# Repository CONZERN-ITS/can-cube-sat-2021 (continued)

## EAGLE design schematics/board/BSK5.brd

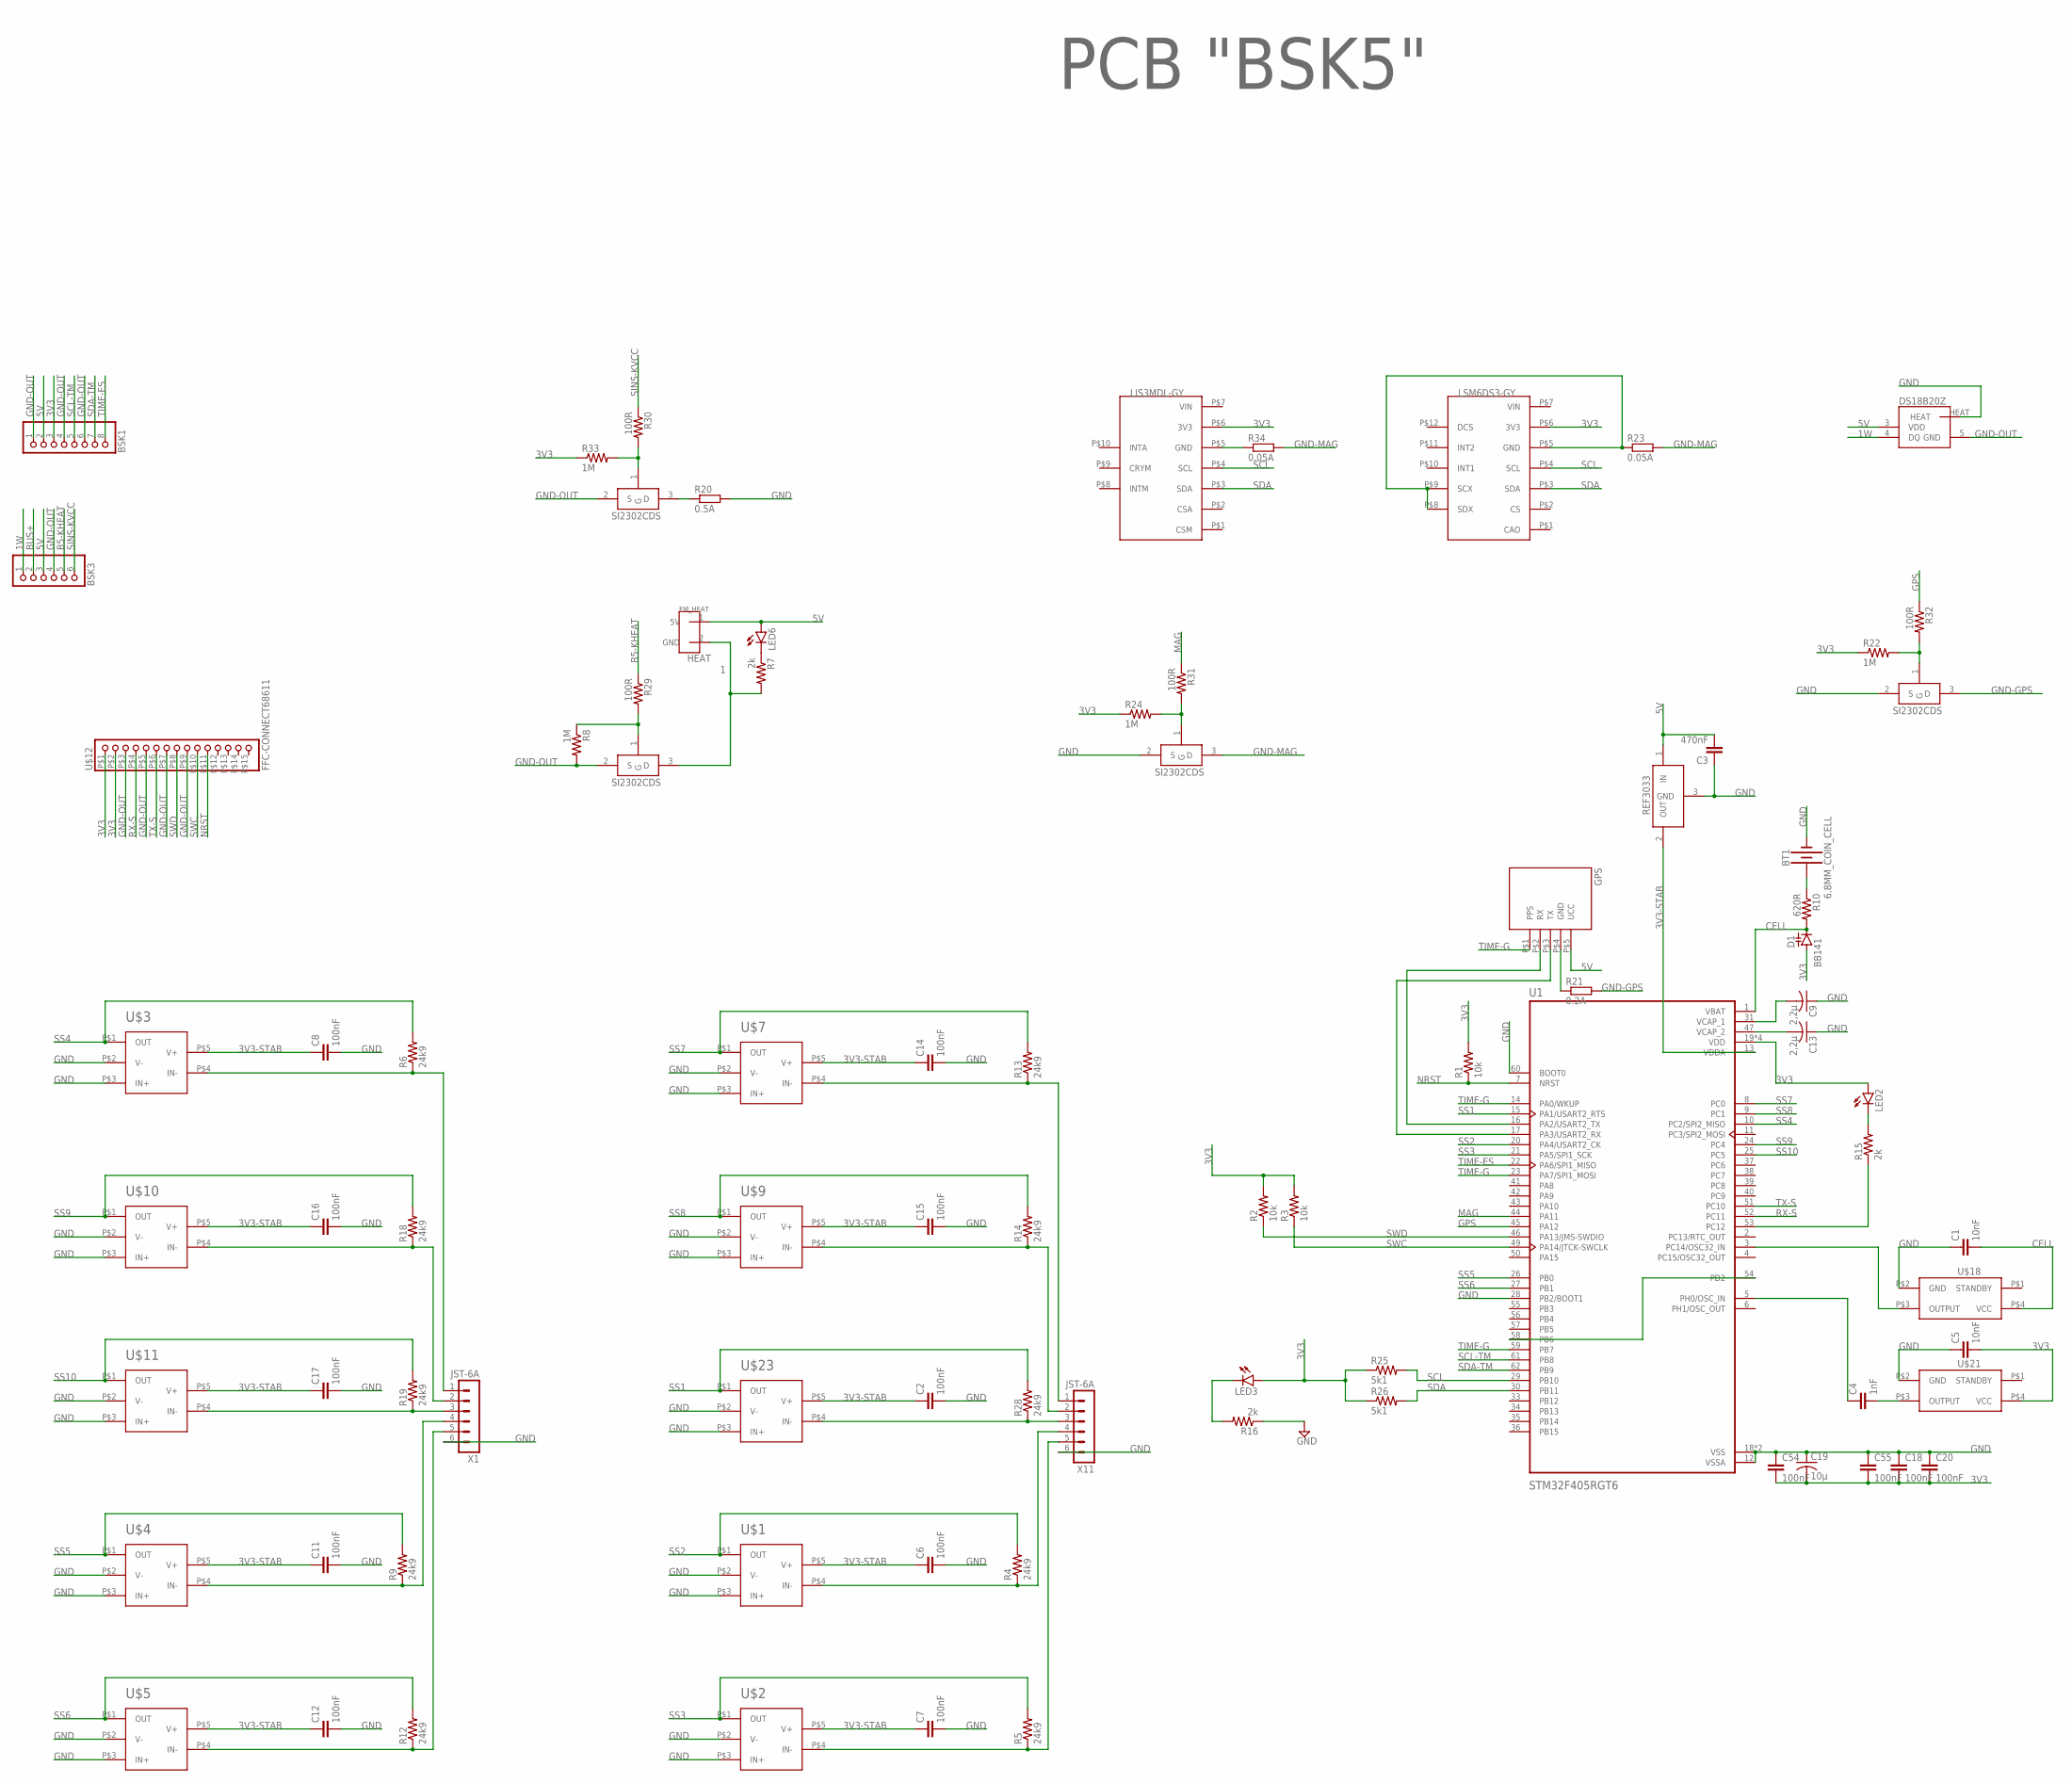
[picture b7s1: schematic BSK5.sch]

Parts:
BSK1: PINHD-1X8; 1X08
BSK3: PINHD-1X6; 1X06
BT1: 6.8MM_COIN_CELL; BATTCON-6.8MM
C1, C5: 10nF; C0603
C2, C6, C7, C8, C11, C12, C14, C15, C16, C17, C18, C20, C54, C55: 100nF; C0603
C3: 470nF; C0603
C4: 1nF; C0603
C9, C13: 2,2µ; C0603
C19: 10µ; C1206
D1: BB141; SOD523
DS18B20Z1: DS18B20Z; SOIC8+HEAT_S
GPS: GPSNEO6M; GPS-NEO6M
LED2, LED3, LED6: LEDCHIPLED_0603; CHIPLED_0603
LIS3MDL-GY: LIS3MDL-GY
LSM6DS3-GY: LSM6DS3-GY
R1, R2, R3: 10k; R0603
R4, R5, R6, R9, R12, R13, R14, R18, R19, R28: 24k9; R0603
R7, R15, R16: 2k; R0603
R8, R22, R24, R33: 1M; R0603
R10: 620R; R0603
R20: 0.5A; R1210
R21: 0.2A; R1210
R23, R34: 0.05A; R1210
R25, R26: 5k1; R0603
R29, R30, R31, R32: 100R; R0603
U1: STM32F405RGT6; QFP50P1200X1200X160-64N
U$1, U$2, U$3, U$4, U$5, U$7, U$9, U$10, U$11, U$23: LMC7101
U$6: REF3033; SOT23-3
U$8, U$19, U$20, U$22: SI2302CDS; SOT23-3
U$12: FFC-CONNECT68611; 68611
U$14: EM_HEAT
U$18: Q32.768
U$21: Q24
U$26: PCB "BSK5"; ITS-LOGO
X1, X11: JST-6A; B6B-EH-A

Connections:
1: R7.2, U$8.3 (D), U$14.2 (GND)
1W: BSK3.1, DS18B20Z1.4 (DQ)
3V3: BSK1.3, C5.2, C18.2, C19.2, C20.2, C54.2, C55.2, D1.A, LED2.A, LED3.A, LIS3MDL-GY.P$6 (3V3), LSM6DS3-GY.P$6 (3V3), R1.2, R2.2, R3.2, R22.1, R24.1, R25.1, R26.1, R33.1, U1.19 (VDD), U1.32 (VDD), U1.48 (VDD), U1.64 (VDD), U$12.P$1 (1), U$12.P$2 (2), U$21.P$4 (VCC)
3V3-STAB: C2.1, C6.1, C7.1, C8.1, C11.1, C12.1, C14.1, C15.1, C16.1, C17.1, U1.13 (VDDA), U$1.P$5 (V+), U$2.P$5 (V+), U$3.P$5 (V+), U$4.P$5 (V+), U$5.P$5 (V+), U$6.2 (OUT), U$7.P$5 (V+), U$9.P$5 (V+), U$10.P$5 (V+), U$11.P$5 (V+), U$23.P$5 (V+)
5V: BSK1.2, BSK3.3, C3.2, DS18B20Z1.3 (VDD), GPS.P$5 (UCC), LED6.A, U$6.1 (IN), U$14.1 (5V)
B5-KHEAT: BSK3.5, R29.1
BUS+: BSK3.2
CELL: C1.2, D1.C, R10.2, U1.1 (VBAT), U$18.P$4 (VCC)
GND: BT1.-, C1.1, C2.2, C3.1, C5.1, C6.2, C7.2, C8.2, C9.1, C11.2, C12.2, C13.1, C14.2, C15.2, C16.2, C17.2, C18.1, C19.1, C20.1, C54.1, C55.1, DS18B20Z1.HEAT, R16.1, R20.2, U1.12 (VSSA), U1.18 (VSS), U1.28 (PB2/BOOT1), U1.60 (BOOT0), U1.63 (VSS), U$1.P$2 (V-), U$1.P$3 (IN+), U$2.P$2 (V-), U$2.P$3 (IN+), U$3.P$2 (V-), U$3.P$3 (IN+), U$4.P$2 (V-), U$4.P$3 (IN+), U$5.P$2 (V-), U$5.P$3 (IN+), U$6.3 (GND), U$7.P$2 (V-), U$7.P$3 (IN+), U$9.P$2 (V-), U$9.P$3 (IN+), U$10.P$2 (V-), U$10.P$3 (IN+), U$11.P$2 (V-), U$11.P$3 (IN+), U$18.P$2 (GND), U$19.2 (S), U$20.2 (S), U$21.P$2 (GND), U$23.P$2 (V-), U$23.P$3 (IN+), X1.6, X11.6
GND-GPS: R21.2, U$20.3 (D)
GND-MAG: R23.2, R34.2, U$19.3 (D)
GND-OUT: BSK1.1, BSK1.4, BSK1.6, BSK3.4, DS18B20Z1.5 (GND), R8.2, U$8.2 (S), U$12.P$3 (3), U$12.P$5 (5), U$12.P$7 (7), U$12.P$9 (9), U$22.2 (S)
GPS: R32.1, U1.45 (PA12)
MAG: R31.1, U1.44 (PA11)
unnamed: U1.3 (PC14/OSC32_IN), U$18.P$3 (OUTPUT)
unnamed: R20.1, U$22.3 (D)
unnamed: R13.1, U$7.P$4 (IN-), X11.1
unnamed: R6.1, U$3.P$4 (IN-), X1.1
unnamed: R9.1, U$4.P$4 (IN-), X1.4
unnamed: R8.1, R29.2, U$8.1 (G)
unnamed: R30.2, R33.2, U$22.1 (G)
unnamed: R24.2, R31.2, U$19.1 (G)
unnamed: LSM6DS3-GY.P$5 (GND), LSM6DS3-GY.P$8 (SDX), LSM6DS3-GY.P$9 (SCX), R23.1
unnamed: R22.2, R32.2, U$20.1 (G)
unnamed: LIS3MDL-GY.P$5 (GND), R34.1
unnamed: BT1.+, R10.1
unnamed: GPS.P$4 (GND), R21.1
unnamed: U1.54 (PD2), U1.58 (PB6)
unnamed: C13.2, U1.47 (VCAP_2)
unnamed: R4.1, U$1.P$4 (IN-), X11.4
unnamed: R5.1, U$2.P$4 (IN-), X11.5
unnamed: LED6.C, R7.1
unnamed: R12.1, U$5.P$4 (IN-), X1.5
unnamed: C9.2, U1.31 (VCAP_1)
unnamed: LED2.C, R15.2
unnamed: R15.1, U1.53 (PC12)
unnamed: LED3.C, R16.2
unnamed: GPS.P$2 (RX), U1.16 (PA2/USART2_TX)
unnamed: GPS.P$3 (TX), U1.17 (PA3/USART2_RX)
unnamed: C4.2, U$21.P$3 (OUTPUT)
unnamed: C4.1, U1.5 (PH0/OSC_IN)
unnamed: R28.1, U$23.P$4 (IN-), X11.3
unnamed: R14.1, U$9.P$4 (IN-), X11.2
unnamed: R18.1, U$10.P$4 (IN-), X1.2
unnamed: R19.1, U$11.P$4 (IN-), X1.3
NRST: R1.1, U1.7 (NRST), U$12.P$11 (11)
RX-S: U1.52 (PC11), U$12.P$4 (4)
SCL: LIS3MDL-GY.P$4 (SCL), LSM6DS3-GY.P$4 (SCL), R25.2, U1.29 (PB10)
SCL-TM: BSK1.5, U1.61 (PB8)
SDA: LIS3MDL-GY.P$3 (SDA), LSM6DS3-GY.P$3 (SDA), R26.2, U1.30 (PB11)
SDA-TM: BSK1.7, U1.62 (PB9)
SINS-KVCC: BSK3.6, R30.1
SS1: R28.2, U1.15 (PA1/USART2_RTS), U$23.P$1 (OUT)
SS2: R4.2, U1.20 (PA4/USART2_CK), U$1.P$1 (OUT)
SS3: R5.2, U1.21 (PA5/SPI1_SCK), U$2.P$1 (OUT)
SS4: R6.2, U1.10 (PC2/SPI2_MISO), U$3.P$1 (OUT)
SS5: R9.2, U1.26 (PB0), U$4.P$1 (OUT)
SS6: R12.2, U1.27 (PB1), U$5.P$1 (OUT)
SS7: R13.2, U1.8 (PC0), U$7.P$1 (OUT)
SS8: R14.2, U1.9 (PC1), U$9.P$1 (OUT)
SS9: R18.2, U1.24 (PC4), U$10.P$1 (OUT)
SS10: R19.2, U1.25 (PC5), U$11.P$1 (OUT)
SWC: R3.1, U1.49 (PA14/JTCK-SWCLK), U$12.P$10 (10)
SWD: R2.1, U1.46 (PA13/JMS-SWDIO), U$12.P$8 (8)
TIME-ES: BSK1.8, U1.22 (PA6/SPI1_MISO)
TIME-G: GPS.P$1 (PPS), U1.14 (PA0/WKUP), U1.23 (PA7/SPI1_MOSI), U1.59 (PB7)
TX-S: U1.51 (PC10), U$12.P$6 (6)

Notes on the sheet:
HEAT

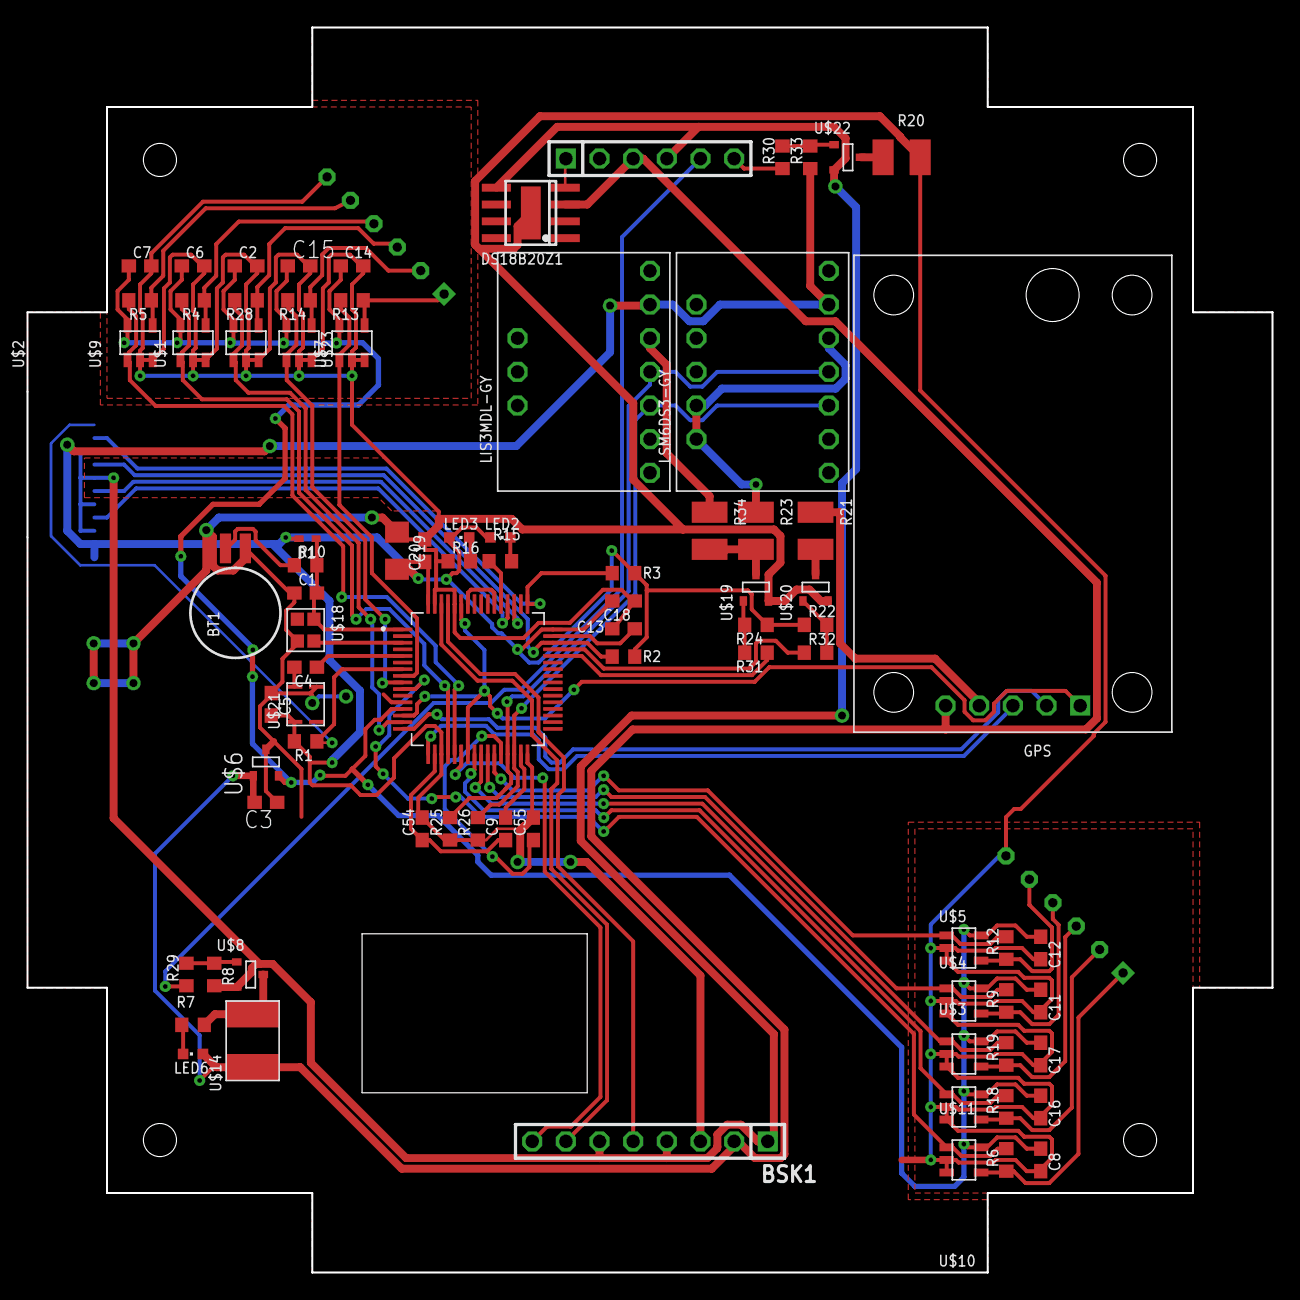
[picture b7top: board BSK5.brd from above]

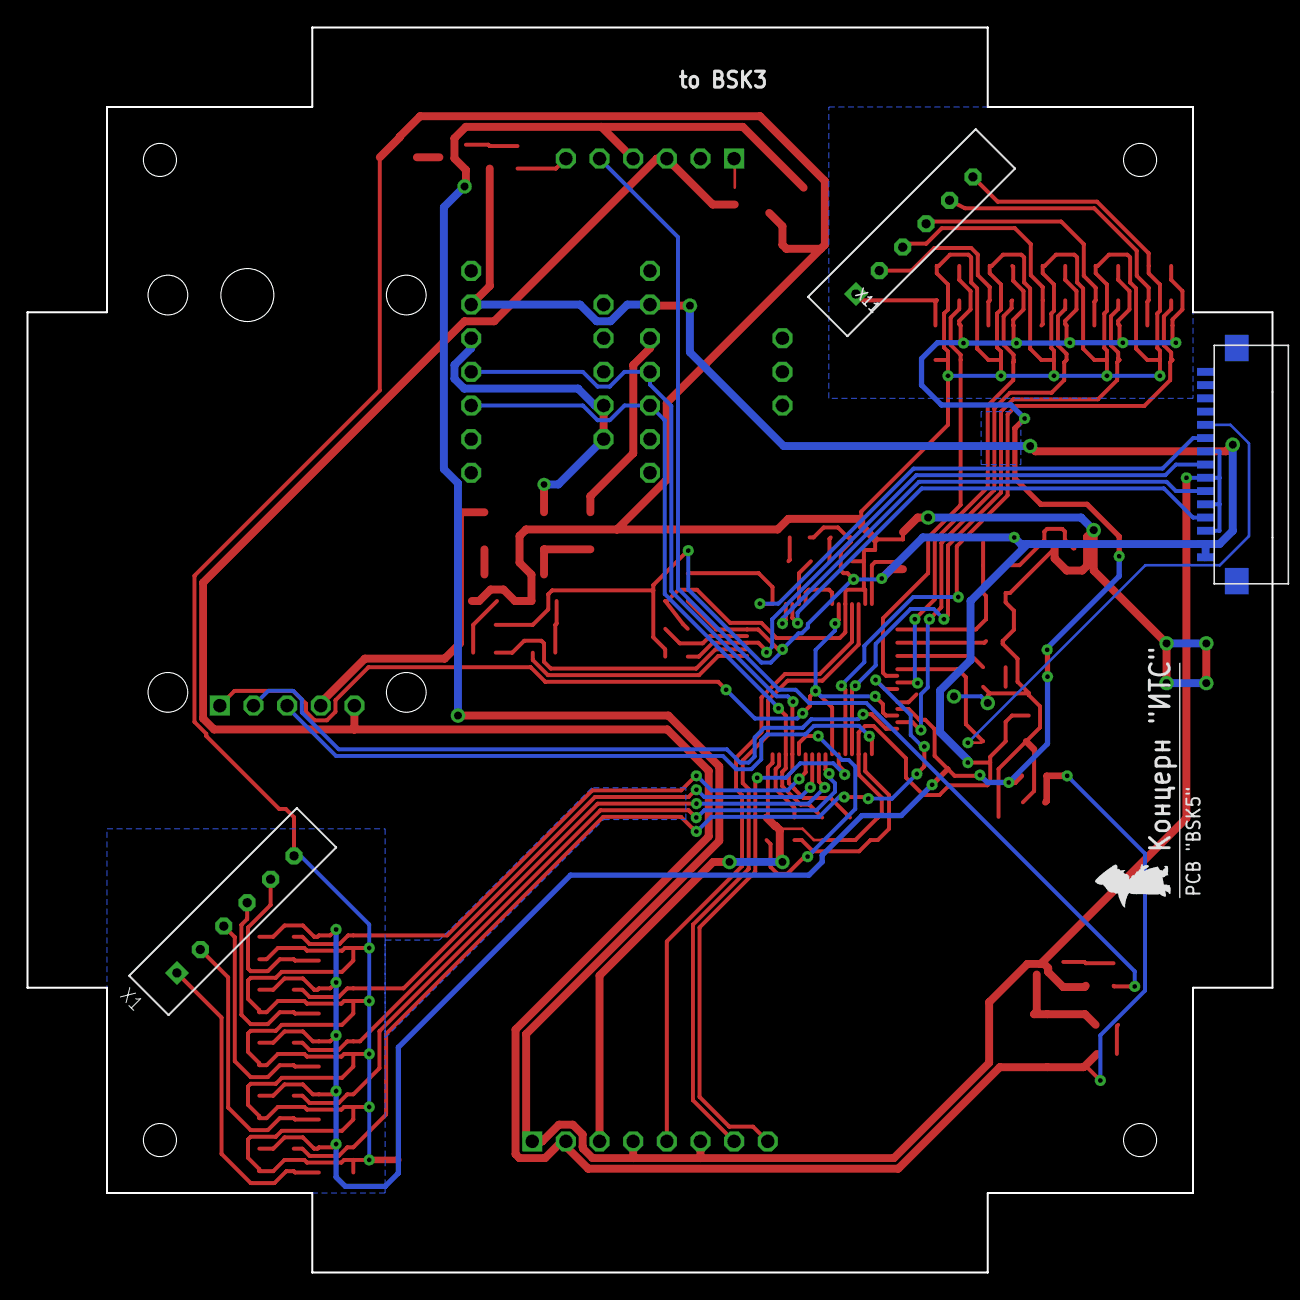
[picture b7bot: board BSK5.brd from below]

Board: 2 copper layers, 94.0 x 94.0 mm, 86 parts (4 on the bottom side), 66 nets.

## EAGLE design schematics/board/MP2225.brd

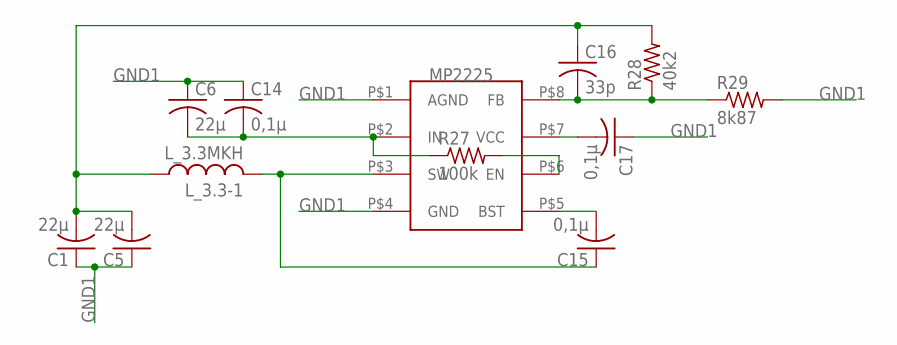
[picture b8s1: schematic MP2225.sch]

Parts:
C1, C5, C6: 22µ; C1206
C14, C15, C17: 0,1µ; C0603
C16: 33p; C0603
L_3.3-1: L_3.3MKH; L_SPM5020
MP2225-1: MP2225; TSOT23-8
R27: 100k; R0603
R28: 40k2; R0603
R29: 8k87; R0603

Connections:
GND1: C1.1, C5.1, C6.1, C14.1, C17.1, MP2225-1.P$1 (AGND), MP2225-1.P$4 (GND), R29.2
unnamed: C1.2, C5.2, C16.1, L_3.3-1.P$1 (1), R28.2
unnamed: C6.2, C14.2, MP2225-1.P$2 (IN), R27.1
unnamed: C15.1, L_3.3-1.P$2 (2), MP2225-1.P$3 (SW)
unnamed: C15.2, MP2225-1.P$5 (BST)
unnamed: MP2225-1.P$6 (EN), R27.2
unnamed: C17.2, MP2225-1.P$7 (VCC)
unnamed: C16.2, MP2225-1.P$8 (FB), R28.1, R29.1

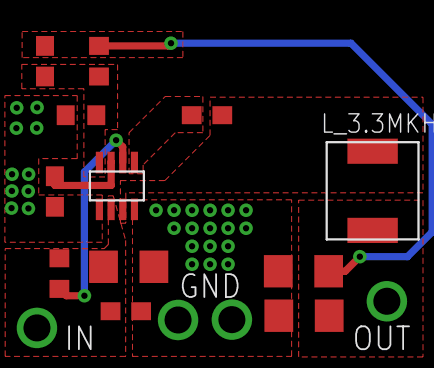
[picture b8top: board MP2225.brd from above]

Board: 2 copper layers, 12 parts (0 on the bottom side), 8 nets.

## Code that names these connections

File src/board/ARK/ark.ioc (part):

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PA2.GPIO_PuPd=GPIO_NOPULL
Mcu.UserName=STM32F103C8Tx
PB10.Mode=I2C
PB14.GPIO_Label=DPC_RST
PA3.GPIO_PuPd=GPIO_NOPULL
PB6.GPIO_ModeDefaultEXTI=GPIO_MODE_IT_FALLING
PA2.GPIO_Speed=GPIO_SPEED_FREQ_LOW
PA3.GPIOParameters=GPIO_Speed,PinState,GPIO_PuPd,GPIO_Label,GPIO_ModeDefaultOutputPP
PA7.GPIO_ModeDefaultOutputPP=GPIO_MODE_OUTPUT_OD
PA6.GPIO_Label=BMS2
PB0.GPIO_Label=PGOOD1
PB6.GPIO_Label=TIME
PA3.GPIO_Speed=GPIO_SPEED_FREQ_LOW
PB11.Signal=I2C2_SDA
PB15.Signal=GPIO_Output
PA5.PinState=GPIO_PIN_SET
PA2.GPIOParameters=GPIO_Speed,PinState,GPIO_PuPd,GPIO_Label,GPIO_ModeDefaultOutputPP
PB15.PinState=GPIO_PIN_SET
RCC.SYSCLKSource=RCC_SYSCLKSOURCE_PLLCLK
PB5.GPIOParameters=GPIO_Speed,PinState,GPIO_PuPd,GPIO_Label,GPIO_ModeDefaultOutputPP
PD1-OSC_OUT.Signal=RCC_OSC_OUT
PA7.PinState=GPIO_PIN_SET
PB1.GPIO_PuPd=GPIO_PULLUP
PB6.Signal=GPXTI6
PB5.PinState=GPIO_PIN_SET
PB15.GPIO_ModeDefaultOutputPP=GPIO_MODE_OUTPUT_PP
PA1.GPIO_PuPd=GPIO_NOPULL
PA4.GPIO_PuPd=GPIO_NOPULL
PA4.GPIO_Speed=GPIO_SPEED_FREQ_LOW
PA2.PinState=GPIO_PIN_SET
PB0.GPIOParameters=GPIO_PuPd,GPIO_Label
PA6.GPIO_PuPd=GPIO_NOPULL
PA1.GPIOParameters=GPIO_Speed,PinState,GPIO_PuPd,GPIO_Label,GPIO_ModeDefaultOutputPP
PA14.Mode=Serial_Wire
PB1.GPIO_Label=PGOOD2
PA5.GPIO_PuPd=GPIO_NOPULL
PB7.Signal=GPIO_Output
PB6.GPIOParameters=GPIO_PuPd,GPIO_Label,GPIO_ModeDefaultEXTI
PB7.PinState=GPIO_PIN_SET
PB7.GPIO_Label=I2C_INT
Mcu.Package=LQFP48
PB9.Signal=I2C1_SDA
PB14.GPIO_PuPd=GPIO_PULLUP
PB1.Signal=GPIO_Input
PA6.Signal=GPIO_Output
PA2.GPIO_ModeDefaultOutputPP=GPIO_MODE_OUTPUT_OD
PB15.GPIO_PuPd=GPIO_PULLUP
PA2.GPIO_Label=BMS6
PA10.Signal=USART1_RX
PA5.GPIOParameters=GPIO_Speed,PinState,GPIO_PuPd,GPIO_Label,GPIO_ModeDefaultOutputPP
PA1.PinState=GPIO_PIN_SET
PB14.GPIOParameters=PinState,GPIO_PuPd,GPIO_Label,GPIO_ModeDefaultOutputPP
PA4.GPIO_ModeDefaultOutputPP=GPIO_MODE_OUTPUT_OD
PA6.GPIO_ModeDefaultOutputPP=GPIO_MODE_OUTPUT_OD
PB5.GPIO_Speed=GPIO_SPEED_FREQ_LOW
PB5.GPIO_Label=LED
PA6.GPIO_Speed=GPIO_SPEED_FREQ_LOW
PA4.GPIO_Label=BMS4
PA3.Signal=GPIO_Output
PB7.GPIO_Speed=GPIO_SPEED_FREQ_HIGH
PA6.GPIOParameters=GPIO_Speed,PinState,GPIO_PuPd,GPIO_Label,GPIO_ModeDefaultOutputPP
PB7.GPIO_PuPd=GPIO_PULLUP
PB5.GPIO_ModeDefaultOutputPP=GPIO_MODE_OUTPUT_OD
PA3.GPIO_ModeDefaultOutputPP=GPIO_MODE_OUTPUT_OD
PD1-OSC_OUT.Mode=HSE-External-Clock-Source
PA10.Mode=Asynchronous
PB6.GPIO_PuPd=GPIO_NOPULL
PA6.PinState=GPIO_PIN_SET
PD0-OSC_IN.Signal=RCC_OSC_IN
PA13.Signal=SYS_JTMS-SWDIO
PA9.Mode=Asynchronous
PB14.PinState=GPIO_PIN_SET
PA4.PinState=GPIO_PIN_SET
PB11.Mode=I2C
PB7.GPIOParameters=GPIO_Speed,PinState,GPIO_PuPd,GPIO_Label,GPIO_ModeDefaultOutputPP
PB9.Mode=I2C
PA9.Signal=USART1_TX
PB14.GPIO_ModeDefaultOutputPP=GPIO_MODE_OUTPUT_OD
PA1.Signal=GPIO_Output
PA7.GPIO_PuPd=GPIO_NOPULL
PD0-OSC_IN.Mode=HSE-External-Clock-Source
PB10.Signal=I2C2_SCL
PB14.Signal=GPIO_Output
PA5.Signal=GPIO_Output
board=custom
PA7.GPIO_Speed=GPIO_SPEED_FREQ_HIGH
PA5.GPIO_ModeDefaultOutputPP=GPIO_MODE_OUTPUT_OD
PB15.GPIO_Label=DPD_RST
PB7.GPIO_ModeDefaultOutputPP=GPIO_MODE_OUTPUT_OD
PA1.GPIO_Speed=GPIO_SPEED_FREQ_LOW
PA1.GPIO_Label=BMS5
PA4.GPIOParameters=GPIO_Speed,PinState,GPIO_PuPd,GPIO_Label,GPIO_ModeDefaultOutputPP
PB15.GPIOParameters=PinState,GPIO_PuPd,GPIO_Label,GPIO_ModeDefaultOutputPP
PA13.Mode=Serial_Wire
Mcu.Name=STM32F103C(8-B)Tx
PA2.Signal=GPIO_Output
PA4.Signal=GPIO_Output
RCC.SYSCLKFreq_VALUE=64000000
PB5.Signal=GPIO_Output
PA7.GPIO_Label=OW
PA5.GPIO_Label=BMS1
PB5.GPIO_PuPd=GPIO_NOPULL
PA14.Signal=SYS_JTCK-SWCLK
PA5.GPIO_Speed=GPIO_SPEED_FREQ_LOW
PB8.Mode=I2C
PB8.Signal=I2C1_SCL
PA3.PinState=GPIO_PIN_SET
PB0.Signal=GPIO_Input
PA7.GPIOParameters=GPIO_Speed,PinState,GPIO_PuPd,GPIO_Label,GPIO_ModeDefaultOutputPP
PB0.GPIO_PuPd=GPIO_PULLUP
PA3.GPIO_Label=BMS3
PB1.GPIOParameters=GPIO_PuPd,GPIO_Label
PA7.Signal=GPIO_Output
PA1.GPIO_ModeDefaultOutputPP=GPIO_MODE_OUTPUT_OD

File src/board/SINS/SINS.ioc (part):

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PH0-OSC_IN.Signal=RCC_OSC_IN
Mcu.UserName=STM32F405RGTx
PB10.Mode=I2C
PC10.Signal=USART3_TX
PA12.GPIOParameters=PinState,GPIO_Label
PC0.GPIOParameters=GPIO_Label
PA11.GPIOParameters=PinState,GPIO_Label
PC0.GPIO_Label=LDiod7
PA3.GPIOParameters=GPIO_Label
PB0.GPIO_Label=LDiod5
PB11.Signal=I2C2_SDA
PA2.GPIOParameters=GPIO_Label
RCC.SYSCLKSource=RCC_SYSCLKSOURCE_PLLCLK
PA12.Signal=GPIO_Output
PC1.GPIOParameters=GPIO_Label
PB6.Signal=S_TIM4_CH1
PH0-OSC_IN.Mode=HSE-External-Clock-Source
PA0-WKUP.GPIOParameters=GPIO_PuPd,GPIO_Label
PA12.PinState=GPIO_PIN_SET
RCC.HSE_VALUE=8000000
PB0.GPIOParameters=GPIO_Label
PA1.GPIOParameters=GPIO_Label
PC14-OSC32_IN.Mode=LSE-External-Clock-Source
PC4.GPIO_Label=LDiod9
PA14.Mode=Serial_Wire
PB1.GPIO_Label=LDiod6
PB7.Signal=S_TIM4_CH2
PH1-OSC_OUT.Mode=HSE-External-Clock-Source
Mcu.Package=LQFP64
PB9.Signal=I2C1_SDA
PB1.Signal=ADCx_IN9
PA6.Signal=S_TIM3_CH1
PA2.GPIO_Label=GPS_UART_TX
PA5.GPIOParameters=GPIO_Label
PC11.Mode=Asynchronous
PB8.GPIO_PuPdOD=GPIO_NOPULL
PC5.Signal=ADCx_IN15
PB10.GPIOParameters=GPIO_PuPdOD
PA4.GPIO_Label=LDiod2
PC2.GPIO_Label=LDiod4
PC4.GPIOParameters=GPIO_Label
PA3.Signal=USART2_RX
PC15-OSC32_OUT.Mode=LSE-External-Clock-Source
PB8.GPIOParameters=GPIO_PuPdOD
PC11.Signal=USART3_RX
PB10.GPIO_PuPdOD=GPIO_NOPULL
PB11.GPIO_PuPdOD=GPIO_NOPULL
PC2.Signal=ADCx_IN12
PC4.Signal=ADCx_IN14
PC10.Mode=Asynchronous
PA11.GPIO_Label=PWR_MEMS
PC0.Signal=ADCx_IN10
PC14-OSC32_IN.Signal=RCC_OSC32_IN
PA12.GPIO_Label=PWR_GPS
PA0-WKUP.GPIO_Label=GPS_PPS_INPUT
PA0-WKUP.Signal=GPXTI0
PB9.GPIOParameters=GPIO_PuPdOD
PA3.Mode=Asynchronous
PA13.Signal=SYS_JTMS-SWDIO
PB11.Mode=I2C
PC5.GPIOParameters=GPIO_Label
PB9.Mode=I2C
PB11.GPIOParameters=GPIO_PuPdOD
PC15-OSC32_OUT.Signal=RCC_OSC32_OUT
PA1.Signal=ADCx_IN1
PB10.Signal=I2C2_SCL
PA5.Signal=ADCx_IN5
board=custom
PC2.GPIOParameters=GPIO_Label
PC1.GPIO_Label=LDiod8
PA1.GPIO_Label=LDiod1
PH1-OSC_OUT.Signal=RCC_OSC_OUT
PA4.GPIOParameters=GPIO_Label
PA13.Mode=Serial_Wire
Mcu.Name=STM32F405RGTx
PA2.Signal=USART2_TX
PA4.Signal=ADCx_IN4
RCC.SYSCLKFreq_VALUE=168000000
PA5.GPIO_Label=LDiod3
PC5.GPIO_Label=LDiod10
PA11.Signal=GPIO_Output
PA14.Signal=SYS_JTCK-SWCLK
PB9.GPIO_PuPdOD=GPIO_NOPULL
PB8.Mode=I2C
PA2.Mode=Asynchronous
PB8.Signal=I2C1_SCL
PA0-WKUP.GPIO_PuPd=GPIO_PULLDOWN
PD2.Signal=S_TIM3_ETR
PA11.PinState=GPIO_PIN_SET
PB0.Signal=ADCx_IN8
PC1.Signal=ADCx_IN11
PA3.GPIO_Label=GPS_UART_RX
PB1.GPIOParameters=GPIO_Label
PA7.Signal=S_TIM3_CH2

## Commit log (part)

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2021-05-29 Миграция пейлоада на новый i2c-link
2021-05-29 Миграция SINS на новый its-i2c-link
2021-05-29 Миграция АРК на новую реализацию its-i2c-link
2021-05-30 Обновление i2c-link драйвера в отладочных проектах с возможностью сборки под f1 и f4
2021-05-30 Ошибка в расчете собственной температуры пейлоада
2021-05-31 Переезд наземных утилиток в отдельную папочку
2021-06-03 Дописал гитингор для тестовых проектов
2021-06-03 Улучшен лог imi в БКУ, исправлены ужасные баги в its-i2c-link
2021-06-03 Новый i2c линк отлажен на синсе
2021-06-03 Новый драйвер АЦП для полезной нагрузки с компенсацией по напряжению на VDDA
2021-06-03 Отчёты комиссара в полезной нагрузке
2021-06-04 Управление компрессором интегрированно в пейлоад. Мавлинк полностью перепахан
2021-06-05 Добавлено монотонное время во все пакеты с борта, кроме GPS_UBX_NAV_TIMEGPS
2021-06-05 Обновлен счетчик резетов, добавлена причина резета. Перетянуты функции чтения и записи в бэкап регистр RTC из LL драйвера
2021-06-05 Мелкие баги в комиссаре
2021-06-05 БКУ в реалиях стабильного времени в каждом сообщении
2021-06-05 Время теперь синхронизиурется
2021-06-05 Новая политика службы времени на полезной нагрузке и расширение её статуса
2021-06-05 Попытка добавить ины
2021-06-07 Ой, перепутал режимы лоры с явным и неявным заголовками
2021-06-08 Мелкие правки сервера-радио. Исправлен не корректный расчет таймаутов
2021-06-09 Не то, чтобы это было страшные баги с радио, но мелочи, которые требовали правки
2021-06-10 Очень нехорошие баги в brd части радио на бку
2021-06-10 опечатка :(
2021-06-10 Добавила ELECTICAL_STATE
2021-06-10 Изменен механизм стирания линий с графика. Теперь не будет ошибок при автомасштабировании, но для стирания необходимо подергать график или окно
2021-06-10 Стыдно
2021-06-10 Переменные надо инициализировать!
2021-06-11 Большая революция в драйвере радио произошла
2021-06-11 Изменены настройки частот для работы с платой
2021-06-11 революция в самом разгаре
2021-06-11 сборка в релизе
2021-06-11 Правки по вдумчивому чтению документации
2021-06-12 Все еще бьет данные
2021-06-12 Снова пробуем работать на sf7
2021-06-12 .launch файлы конкретно надоели
2021-06-12 Ины работают (только макс значение тока надо редактировать)
2021-06-12 Рабочее радио
2021-06-12 GPS было слишком частым
2021-06-12 Акутализация радио параметров для Земли
2021-06-12 Новые логи БКУ
2021-06-12 Добавила в настройки отображение rssi и нового пакетв с состоянием
2021-06-12 Увеличил количество логов БКУ
2021-06-12 Подправила Drive_control. Теперь двигатели можно добавлять при инициализации.
2021-06-12 Вырезала time_steady из сообщений
2021-06-12 Добавлены логи оператора и радио
2021-06-12 Добавила возможность получчить словарь с ограничителями от drive control
2021-06-15 Ой, файл server.c взялся не из той ветки
2021-06-16 Общие функции вынесены в общий класс, добавлен таймаут по моторам(функция для АС "Лук" не работает)
2021-06-16 Ошибка в вызове функции родительского класса
2021-06-16 Исправлен родительский класс, добавлен минимальный угол поворота
2021-06-16 В интерфейс контроля добавлены недостающие аргументы
2021-06-16 Исправлены ошибки в названиях методов и переменных, добавлен park для интерфейса антенны
2021-06-16 Попытка заставить ины работать так, как задумывалось
2021-06-16 Молчать!
2021-06-16 CSS более менее оформлено
2021-06-17 Правильный подсчет размера коррекции времени
2021-06-17 Ина как-то работает?
2021-06-17 Ины работают отменно
2021-06-17 Логи теперь еще более безопасные
2021-06-17 Доработка утилит разбора телеметрии для анализа потока наверх
2021-06-18 Убрано лишнее и добавлена возможность убрать из отображения комманду (актуально только для списка незавершенных)
2021-06-19 Добавила еще ин в отображение
2021-06-19 Обновила конфиг в соответствии с новой распиновкой
2021-06-19 requirements для мавлинка. Пусть тоже будет
2021-06-19 Логфайл поддерживает более точное время
2021-06-19 Нагреватеели теперь работают
2021-06-19 Больше дсок!
2021-06-19 Оказывается, порядок сдивговых регистров другой :(
2021-06-19 Лишний перевод на новую строку
2021-06-20 Проекты для ОЧЕРЕДНОЙ отработки лоры
2021-06-20 Правки мелких и не сильно существенных багов в драйвере радио
2021-06-20 В метаданные сервера-радио добавлено время
2021-06-20 Кажется, наконец-то правильная реализация воркэрануда 4 для радио и задержка в секунду перед запуском проекта-спамера для устаканивания питания
2021-06-20 Опечаточки в JSONe от сервера
2021-06-20 Стрела МС теперь умеет выгребать время из метаданных ZMQ сообщений.
    В настройки STATE панели добавлено сообщение со статусом радио
    P.S почему-то в консоли валятся сообщения list index is out of range
2021-06-23 Исправлены опечатки и добавлены недостающие моули
2021-06-23 Добавлена поддержка номера фрейма в сервере-радио
2021-06-23 Еще немного исправлений опечаток
2021-06-23 Дописаны настройки
2021-06-23 Номер пакета
2021-06-23 Больше логов
2021-06-23 обновлена документация по сообщению radio.downlink_frame
2021-06-23 ОБНОВЛЕНИЕ МАВЛИНКА. Ремонт службы времени на пейлоаде и расширенная диагностика в телеметрии.
2021-06-24 Баг с утечкой памяти и не только
2021-06-24 Подкорректировали СД
2021-06-24 Почистил код
2021-06-25 Запуск с RTC. Работает
2021-06-25 Добавлено время в человекочитаемом формате
2021-06-25 Перенесено условие, необходимое для автоматического управления. Теперь оно не должно мешать ручному
2021-06-25 Исправлены опечатки в коде, отвечающем за математику. Теперь оно хотя бы запускается
2021-06-25 МАВЛИНК. Новая команда
2021-06-25 Обработка новых команд
2021-06-25 МАВЛИНК. Номер последней команды
2021-06-25 Убран варнинг
2021-06-25 Заготовки для безопасного радио
2021-06-25 Название переменной приведено в соответствие
2021-06-25 Убран принт и исправлены аргументы setup_location
2021-06-26 исправлена лампочка для платы ark
2021-06-26 Добавила счетчик беддаты
2021-06-26 Температуры передвинула на график температур, Напрядения вывела отдельно
2021-06-26 Возвращена проверка валидности пакетов gps
2021-06-26 Реализована поддержка CSS на PAYLOAD
2021-06-26 Доработки
2021-06-26 Добавила данные PCU
2021-06-26 Добавила обратную связь для реакции на сообщение, переписала жесткое управление, переписала расчет углов поворота и исправила ошибку в их расчете, из-за которой не производилось полное наведение на у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
2021-06-29 Адреса на пейлоаде исправлены
2021-06-29 Попытка уменьшить лаг отправки времени с синса
2021-06-29 Новые сообщения для фильтрации + изменила id комманд
2021-06-29 Таакая частота вроде тоже работает
2021-06-29 Комментарии к службе времени на синсе
2021-06-30 Интегрировала фильтр для GPS
2021-06-30 Мелкие вставки для всяких проверок и диагностики. Коммичу, чтобы были у всех, так как это сейчас зашито
2021-07-01 Добавила фильтр для GPS + Добавила больше RSSI
2021-07-01 Исправлены ошибки, связанные с добавлением gps фильтра
2021-07-02 Заготовка для модуля, управляющего питанием
2021-07-02 Частота синса исправлена
2021-07-02 Логгер + подсчет потерянных пакетов
2021-07-02 Пусть куки идет с 1, не будем заморачиваться
2021-07-02 Поддержка сброса пакетов не подходящих по времени в its-logfile-player
2021-07-02 Управление питанием теперь работает
2021-07-02 Упси
2021-07-03 Исправлен пакет с ошибками
2021-07-03 Добавлена статистика по синхронизации времени
2021-07-03 Добавлено в ARK: проверка timebase, сборка статистики по синхронизации времени, счетчик резетов
2021-07-03 Добавлено оконное измерение дозиметром
2021-07-03 Очень нехорошая ошибка с отправкой данных дозиметра
2021-07-03 Коррекция температур для ДНК
2021-07-03 Еще одна очень нехорошая ошибка в коде дозиметра
2021-07-03 Починил синхронизацию времени
2021-07-03 Наконец-то дал этому модулю нормальное имя
2021-07-03 Закрывает https://conzern-its.myjetbrains.com/youtrack/issue/CCS2021-124
2021-07-06 ой! Это должно было быть в прошлом коммите
2021-07-07 Добавлен приоритет для этапов
2021-07-07 Исправлена ошибка в названии переменной
2021-07-07 Исправлены недочеты в фильтре gps
2021-07-07 Фиксим статистику времени
2021-07-07 Забытое время пакета
2021-07-07 Тсссс! Тише!
2021-07-07 Игры с количеством буферов SINS и приоритетами выдачи сообещений
2021-07-07 Созданы гербер файлы AB и RADIO
2021-07-07 Тащемта выгружены все STL модели
2021-07-07 Удалена старая папка
2021-07-07 Добавлен robust_parsing
2021-07-07 Починен сброс для sx126x на БКУ
2021-07-10 Исправлен счетчик потеряных пакетов
2021-07-10 Добавил алгоритм расчета положения солнца
2021-07-12 Кто-то не умеет вызывать функции. Должно исправлять не взятие времени gps https://conzern-its.myjetbrains.com/youtrack/issue/CCS2021-131
2021-07-12 Закончен солнечный датчик
2021-09-01 Исправления драйвера ины и использование правильных сопротивлений
2021-09-03 Радио теперь передает пакеты, которые накапливаются и во время получения
2021-09-08 Включен вотчдог
2021-09-08 Починили термодатчики
2021-09-11 Проект с расчетом параметров алгоритма управления компрессором (не понял почему он не был включен?)
2021-09-11 Реворк I2C таска на арке
2021-09-11 !MAVLINK! Новое сообщение для солнечного датчика
2021-09-11 В i2c-link-stats на арке забыто время
2021-09-11 Ины теперь должны перезагружаться при получении от них плохих данных
2021-09-11 Вот так указ работает, Это правильно?
2021-09-11 Добавлены сообщения со статистикой ITS_I2C_LINK на STATE формат стрелы мс
2021-09-15 Уменьшаем количество выводимых логов
2021-09-15 Радио теперь готово отправлять сразу после запуска. И буфер побольше
2021-09-15 СД карта теперь быстрее восстанавливается
2021-09-15 Убрана подтяжка на OW
2021-09-15 Этот дефайн больше не используется
2021-09-15 pdTRUE = 1 а pdFALSE = 0. Просто ужас
2021-09-16 Добавлен вспомогательный кодик для тестов компрессора
2021-09-16 Доделал форвардер пакетов. Нужна проверка
2021-09-16 Добавлены проекты gnu-radio-companion для приёма пакетов наших команд
2021-09-18 Добавила новую модель
2021-09-18 Изменила описание ошибки
2021-09-18 Добавила sdr
2021-09-18 Отредактирован лора-проект для гнурадио. Доделан скрипт sdr-forwarder. топик sdr.downlink_frame документирован
2021-09-18 Доделана система установки мощности. В процессе тестирования
2021-09-18 Система работает
2021-09-18 Еще одна попытка исправить баг
2021-09-18 Улучшение внешнего вида
2021-09-18 Добавил высоту по GPS на график барометрической высоты
2021-09-18 Posix структура tm просто отвратительна
2021-09-20 Актуализация документации по топикам и небольшое причесывание сервера-радио
2021-09-24 Улучшенное управление включением магнитометра в AHRS
2021-09-24 Улушчение лога сервера-радио
2021-09-24 Украшение скрипта для обновления pa_power
2021-09-24 Теперь то работает
2021-09-24 Унифицировал сдр-форвардер скрипт
2021-09-25 Реворк рекавера i2c шины с инами на арке
2021-09-25 Перестаем качать компрессором с 12ти километров и оставляем только продувку. А еще обновлена модель для проверки компрессора
2021-09-25 Добавила несколько мест накопления мавлин пакетов для разных топиков, добавила принты и пересчет во флоты
2021-09-25 Актуализированы настройки, добавлены графики расстояния и высоты для синс
2021-09-25 Исправление ошибки с отправкой сообщения
2021-09-25 Почему-то в коммит попала несвежая версия, исправляю. Надо протестить
2021-10-01 Правильное направление магнитометра
2021-10-01 МАВЛИНК! Объеденинены сообщения ИНС
2021-10-01 Исправленный солнечный датчик
2021-10-01 В настройках поменяла SINS_AHRS_STATS, LIGHT_DIODE, LDS_DIR на SINS_isc в соответствии с новой версией мавлинк
2021-10-01 Поправила график солнечного датчика
2021-10-01 Добавлена отсечка показаний bme280 от алгоритмов управления, в случае, если его показания уходят за пределы допустимых по даташиту
2021-10-02 Обновлен Мавлинк, добавлен недобавленный файл, улучшен ИНС
2021-10-02 Батники для программ
2021-10-02 Подтачиваем ПЛ
2021-10-03 Работаем над управлением компрессора в условиях хорошей утечки из гермообъема
2021-10-03 более серьезная модификация
2021-10-04 Апгрейд алгоритма управления компрессором на пейлоаде
2021-10-05 Палетная телеметрия SD
2021-10-05 Доброс актуальной полётной конфигурации
2021-10-05 Телеметрия наземной станции
2021-10-05 Скрипты для разбора метаданных брокера научились делать csv
2021-10-05 .csv файлы для метаданных брокера исправлены (time_gregororian теперь действительно gregorian) и порядок полей сделан привычно
2021-10-05 Телеметрия с пофикшенным временем
2021-10-05 Сделал sqlite БД из всей телеметрии и отдельно сделал участок с монотонным подъемом и началом падения до замерзания
2021-10-08 Изменена папка для аудио файлов
2021-10-08 Забытый актуальный код модели компрессора
